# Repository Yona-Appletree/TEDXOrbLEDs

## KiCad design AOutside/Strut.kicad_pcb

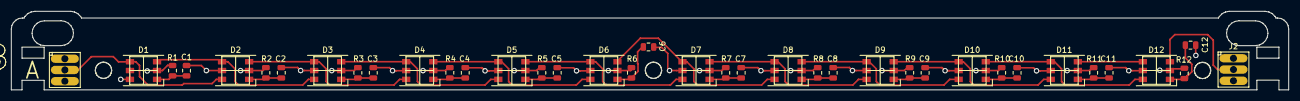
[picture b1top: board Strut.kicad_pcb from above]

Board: 4 copper layers, 231.2 x 14.2 mm, 38 parts (0 on the bottom side), 27 nets.

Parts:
C1, C2, C3, C4, C5, C6, C7, C8, C9, C10, C11, C12: 100NF; C_0805_2012Metric
D1, D2, D3, D4, D5, D6, D7, D8, D9, D10, D11, D12: WS2813; LED_WS2812_PLCC6_5.0x5.0mm_P1.6mm
J1: A_IN; 1x3_18awgWireSolderPad-5mm
J2: A_OUT; 1x3_18awgWireSolderPad-5mm
R1, R2, R3, R4, R5, R6, R7, R8, R9, R10, R11, R12: 330; R_0805_2012Metric

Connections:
+5V: D1.2, D2.2, D3.2, D4.2, D5.2, D6.2, D7.2, D8.2, D9.2, D10.2, D11.2, D12.2, J1.1, J2.1, R1.1, R2.1, R3.1, R4.1, R5.1, R6.1, R7.1, R8.1, R9.1, R10.1, R11.1, R12.1
GND: C1.2, C2.2, C3.2, C4.2, C5.2, C6.2, C7.2, C8.2, C9.2, C10.2, C11.2, C12.2, D1.5, D1.6, D2.5, D3.5, D4.5, D5.5, D6.5, D7.5, D8.5, D9.5, D10.5, D11.5, D12.5, J1.3, J2.3
unnamed: C1.1, D1.1, R1.2
unnamed: C2.1, D2.1, R2.2
unnamed: C3.1, D3.1, R3.2
unnamed: C4.1, D4.1, R4.2
unnamed: C5.1, D5.1, R5.2
unnamed: C6.1, D6.1, R6.2
unnamed: C7.1, D7.1, R7.2
unnamed: C8.1, D8.1, R8.2
unnamed: C9.1, D9.1, R9.2
unnamed: C10.1, D10.1, R10.2
unnamed: C11.1, D11.1, R11.2
unnamed: C12.1, D12.1, R12.2
unnamed: D1.3, D2.4, D3.6
unnamed: D1.4, D2.6, J1.2
unnamed: D2.3, D3.4, D4.6
unnamed: D3.3, D4.4, D5.6
unnamed: D4.3, D5.4, D6.6
unnamed: D5.3, D6.4, D7.6
unnamed: D6.3, D7.4, D8.6
unnamed: D7.3, D8.4, D9.6
unnamed: D10.3, D11.4, D12.6
unnamed: D9.3, D10.4, D11.6
unnamed: D8.3, D9.4, D10.6
unnamed: D11.3, D12.4
unnamed: D12.3, J2.2
